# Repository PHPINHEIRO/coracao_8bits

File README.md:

# coracao_8bits
um projeto de uma relogio usando um display de 7 segmentos + arduino pro mini e RTC em formato de um coracao em graficos de 8bits

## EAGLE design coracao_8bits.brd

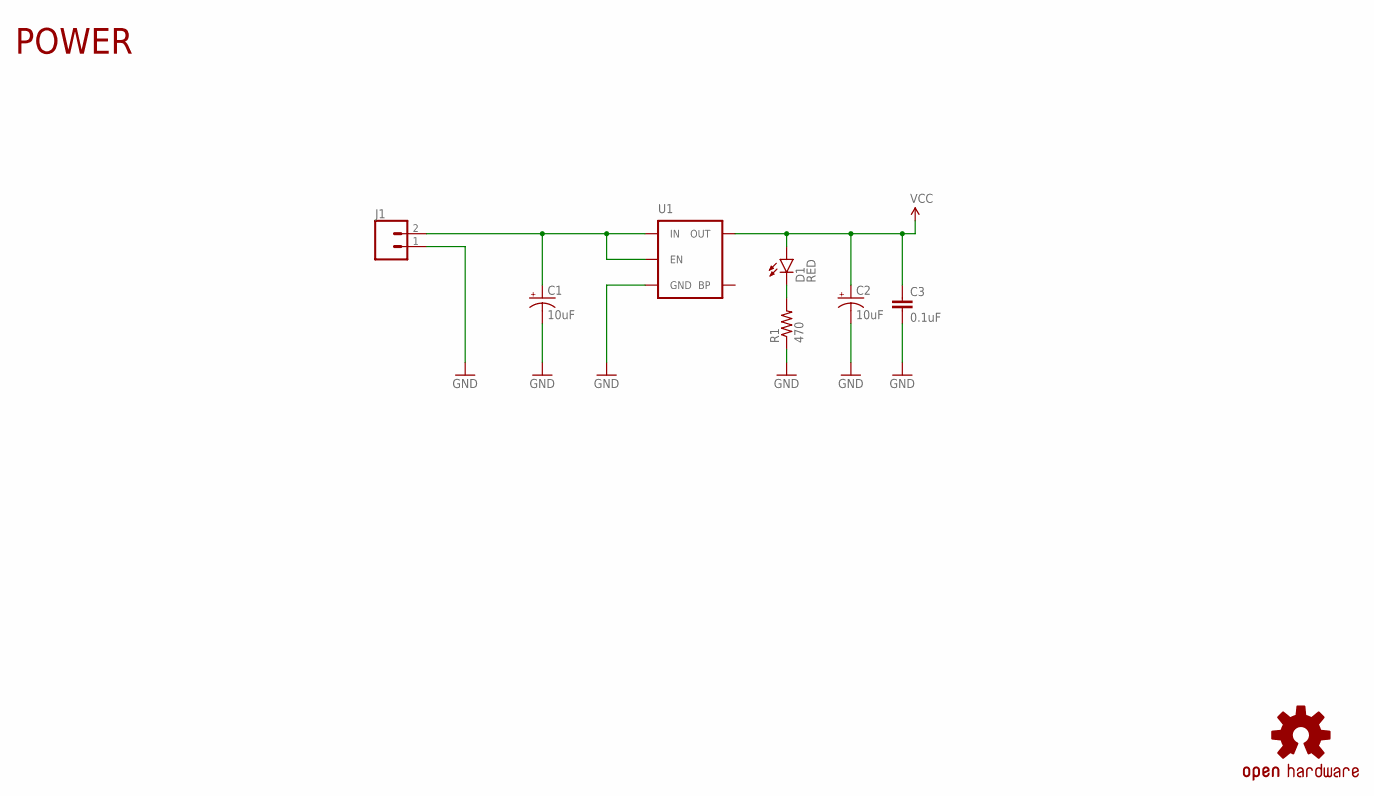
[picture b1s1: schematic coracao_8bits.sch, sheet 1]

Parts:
C1, C2: 10uF; EIA3216
C3: 0.1uF; 0603-CAP
D1: RED; LED-0603
J1: CONN_02; 1X02
LOGO1: OSHW-LOGOMINI; OSHW-LOGO-MINI
R1: 470; 0603-RES
U1: MIC52053.3V; SOT23-5

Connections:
DEETE: C1.A (+), J1.2, U1.1 (IN), U1.3 (EN)
GND: C1.C (-), C2.C (-), C3.2, J1.1, R1.1, U1.2 (GND); also elsewhere on the board
unnamed: D1.C, R1.2
VCC: C2.A (+), C3.1, D1.A, U1.5 (OUT); also elsewhere on the board

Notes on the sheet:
POWER

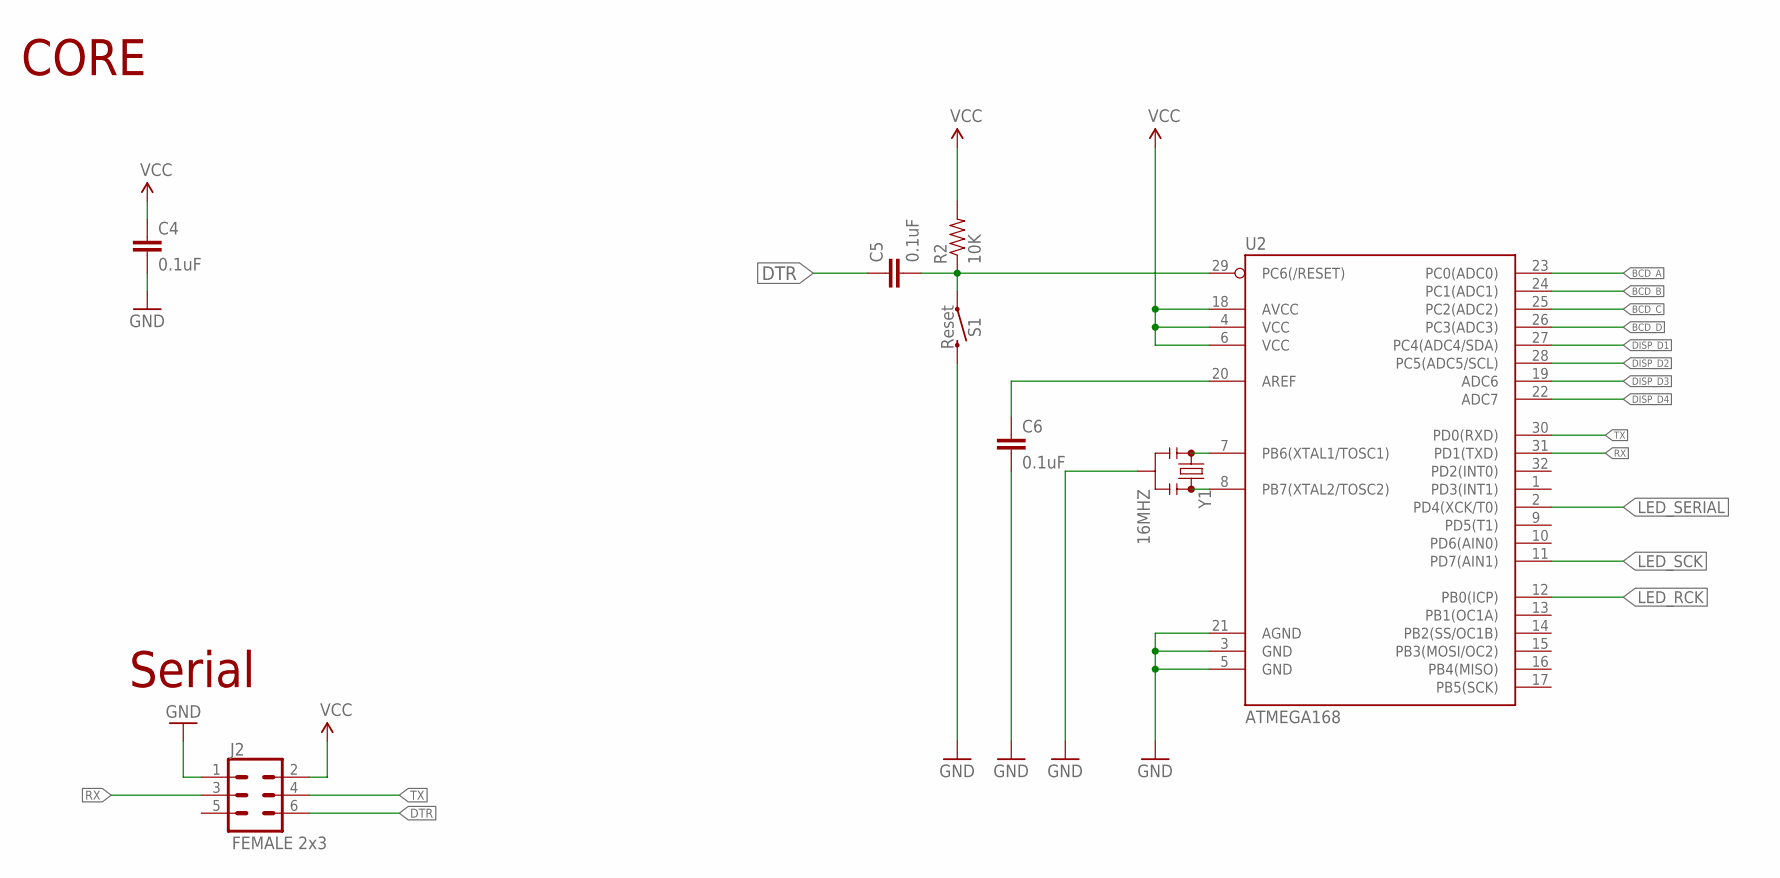
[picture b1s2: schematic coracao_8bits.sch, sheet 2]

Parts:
C4, C5, C6: 0.1uF; 0603-CAP
J2: FEMALE 2x3; 2X3
R2: 10K; 0603-RES
S1: Reset; TACTILE_SWITCH_SMD_6.0X3.5MM
U2: ATMEGA168; TQFP32-08
Y1: 16MHZ; RESONATOR-SMD

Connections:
BCD_A: U2.23 (PC0(ADC0)); also elsewhere on the board
BCD_B: U2.24 (PC1(ADC1)); also elsewhere on the board
BCD_C: U2.25 (PC2(ADC2)); also elsewhere on the board
BCD_D: U2.26 (PC3(ADC3)); also elsewhere on the board
DISP_D1: U2.27 (PC4(ADC4/SDA)); also elsewhere on the board
DISP_D2: U2.28 (PC5(ADC5/SCL)); also elsewhere on the board
DISP_D3: U2.19 (ADC6); also elsewhere on the board
DISP_D4: U2.22 (ADC7); also elsewhere on the board
DTR: C5.1, J2.6
GND: C4.2, C6.2, J2.1, S1.2, U2.3 (GND), U2.5 (GND), U2.21 (AGND), Y1.2; also elsewhere on the board
LED_RCK: U2.12 (PB0(ICP)); also elsewhere on the board
LED_SCK: U2.11 (PD7(AIN1)); also elsewhere on the board
LED_SERIAL: U2.2 (PD4(XCK/T0)); also elsewhere on the board
unnamed: U2.7 (PB6(XTAL1/TOSC1)), Y1.1
unnamed: U2.8 (PB7(XTAL2/TOSC2)), Y1.3
unnamed: C6.1, U2.20 (AREF)
unnamed: C5.2, R2.1, S1.1, U2.29 (PC6(/RESET))
RX: J2.3, U2.31 (PD1(TXD))
TX: J2.4, U2.30 (PD0(RXD))
VCC: C4.1, J2.2, R2.2, U2.4 (VCC), U2.6 (VCC), U2.18 (AVCC); also elsewhere on the board

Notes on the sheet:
CORE
Serial

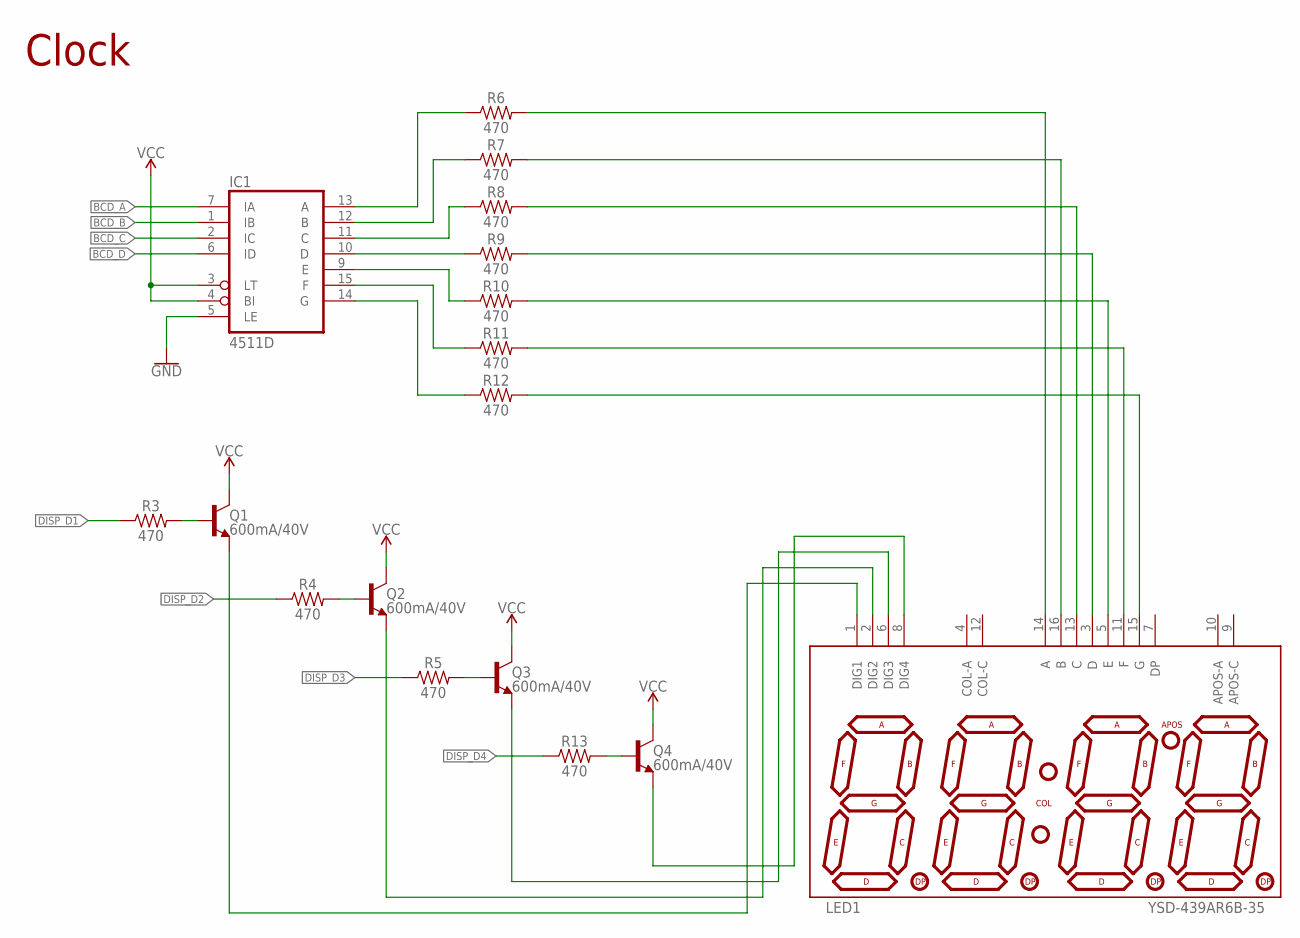
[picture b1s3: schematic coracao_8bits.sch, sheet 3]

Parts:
IC1: 4511D; SO16
LED1: YSD-439AR6B-35; 7-SEGMENT-4DIGIT-YOUNGSUN
Q1, Q2, Q3, Q4: 600mA/40V; SOT23-3
R3, R4, R5, R6, R7, R8, R9, R10, R11, R12, R13: 470; 0603

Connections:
BCD_A: IC1.7 (IA); also elsewhere on the board
BCD_B: IC1.1 (IB); also elsewhere on the board
BCD_C: IC1.2 (IC); also elsewhere on the board
BCD_D: IC1.6 (ID); also elsewhere on the board
DISP_D1: R3.1; also elsewhere on the board
DISP_D2: R4.1; also elsewhere on the board
DISP_D3: R5.1; also elsewhere on the board
DISP_D4: R13.1; also elsewhere on the board
GND: IC1.5 (LE); also elsewhere on the board
unnamed: IC1.10 (D), R9.1
unnamed: IC1.11 (C), R8.1
unnamed: IC1.12 (B), R7.1
unnamed: IC1.13 (A), R6.1
unnamed: IC1.9 (E), R10.1
unnamed: IC1.15 (F), R11.1
unnamed: IC1.14 (G), R12.1
unnamed: LED1.14 (A), R6.2
unnamed: LED1.16 (B), R7.2
unnamed: LED1.13 (C), R8.2
unnamed: LED1.3 (D), R9.2
unnamed: LED1.5 (E), R10.2
unnamed: LED1.11 (F), R11.2
unnamed: LED1.15 (G), R12.2
unnamed: LED1.8 (DIG4), Q4.2 (E)
unnamed: LED1.6 (DIG3), Q3.2 (E)
unnamed: LED1.2 (DIG2), Q2.2 (E)
unnamed: LED1.1 (DIG1), Q1.2 (E)
unnamed: Q2.1 (B), R4.2
unnamed: Q4.1 (B), R13.2
unnamed: Q3.1 (B), R5.2
unnamed: Q1.1 (B), R3.2
VCC: IC1.3 (LT), IC1.4 (BI), Q1.3 (C), Q2.3 (C), Q3.3 (C), Q4.3 (C); also elsewhere on the board
VDD: IC1.16 (VDD)
VSS: IC1.8 (VSS)

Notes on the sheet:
Clock

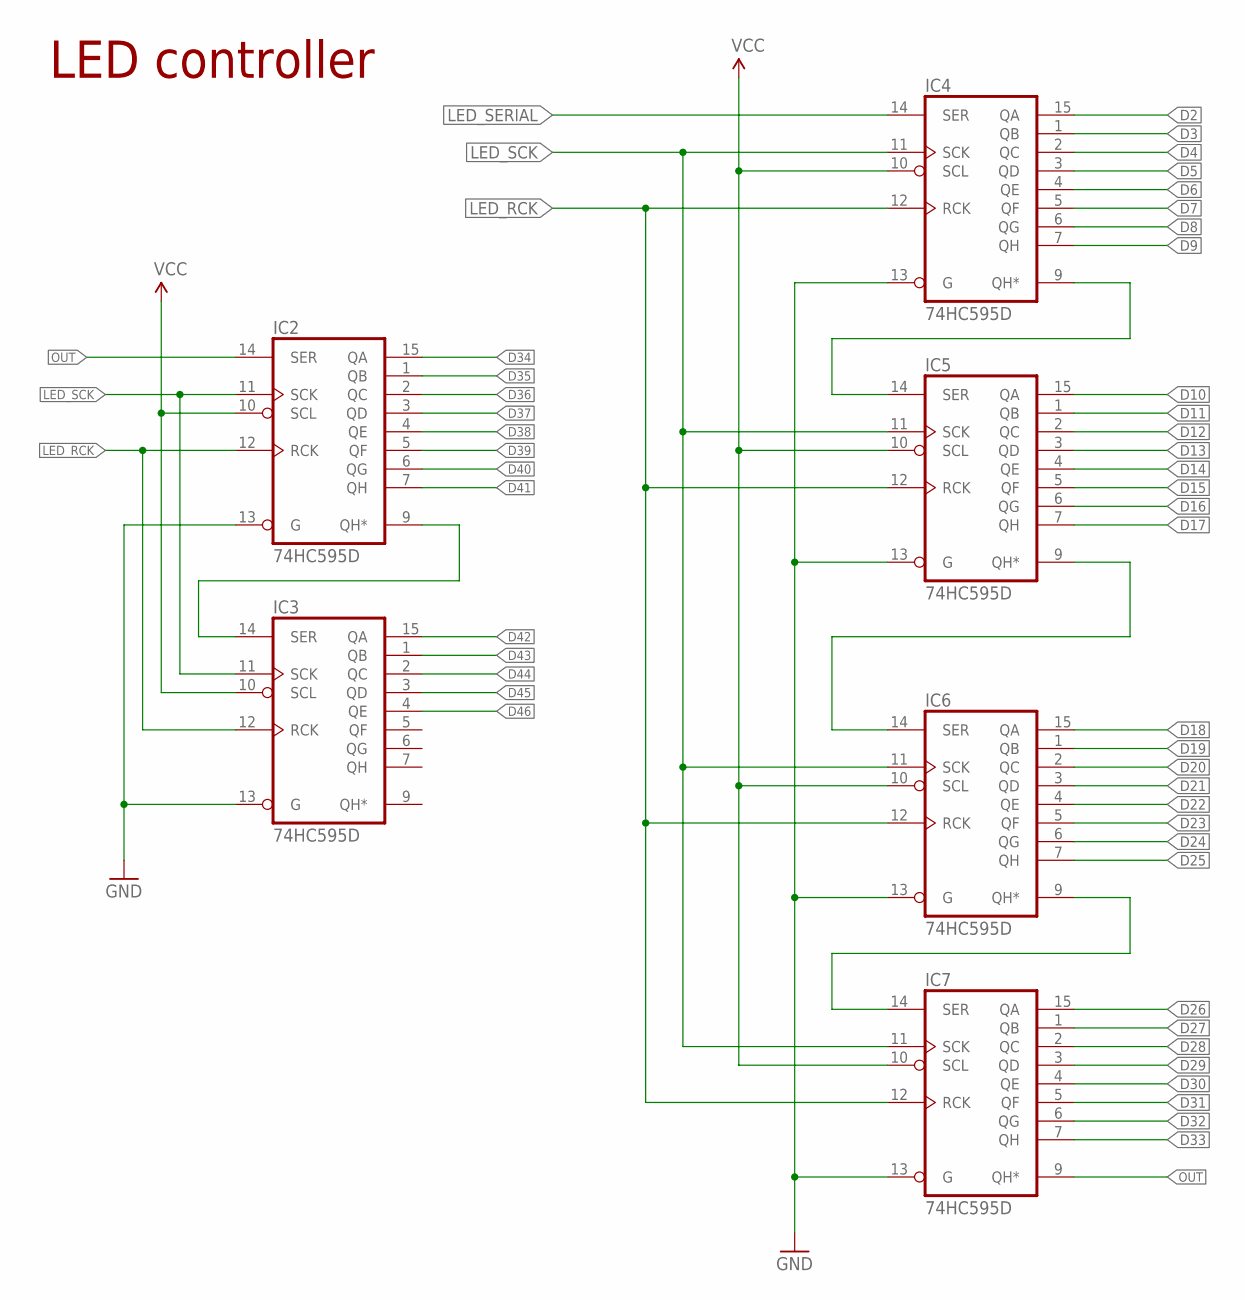
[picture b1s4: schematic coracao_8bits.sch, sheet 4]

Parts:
IC2, IC3, IC4, IC5, IC6, IC7: 74HC595D; SO16

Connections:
D2: IC4.15 (QA); also elsewhere on the board
D3: IC4.1 (QB); also elsewhere on the board
D4: IC4.2 (QC); also elsewhere on the board
D5: IC4.3 (QD); also elsewhere on the board
D6: IC4.4 (QE); also elsewhere on the board
D7: IC4.5 (QF); also elsewhere on the board
D8: IC4.6 (QG); also elsewhere on the board
D9: IC4.7 (QH); also elsewhere on the board
D10: IC5.15 (QA); also elsewhere on the board
D11: IC5.1 (QB); also elsewhere on the board
D12: IC5.2 (QC); also elsewhere on the board
D13: IC5.3 (QD); also elsewhere on the board
D14: IC5.4 (QE); also elsewhere on the board
D15: IC5.5 (QF); also elsewhere on the board
D16: IC5.6 (QG); also elsewhere on the board
D17: IC5.7 (QH); also elsewhere on the board
D18: IC6.15 (QA); also elsewhere on the board
D19: IC6.1 (QB); also elsewhere on the board
D20: IC6.2 (QC); also elsewhere on the board
D21: IC6.3 (QD); also elsewhere on the board
D22: IC6.4 (QE); also elsewhere on the board
D23: IC6.5 (QF); also elsewhere on the board
D24: IC6.6 (QG); also elsewhere on the board
D25: IC6.7 (QH); also elsewhere on the board
D26: IC7.15 (QA); also elsewhere on the board
D27: IC7.1 (QB); also elsewhere on the board
D28: IC7.2 (QC); also elsewhere on the board
D29: IC7.3 (QD); also elsewhere on the board
D30: IC7.4 (QE); also elsewhere on the board
D31: IC7.5 (QF); also elsewhere on the board
D32: IC7.6 (QG); also elsewhere on the board
D33: IC7.7 (QH); also elsewhere on the board
D34: IC2.15 (QA); also elsewhere on the board
D35: IC2.1 (QB); also elsewhere on the board
D36: IC2.2 (QC); also elsewhere on the board
D37: IC2.3 (QD); also elsewhere on the board
D38: IC2.4 (QE); also elsewhere on the board
D39: IC2.5 (QF); also elsewhere on the board
D40: IC2.6 (QG); also elsewhere on the board
D41: IC2.7 (QH); also elsewhere on the board
D42: IC3.15 (QA); also elsewhere on the board
D43: IC3.1 (QB); also elsewhere on the board
D44: IC3.2 (QC); also elsewhere on the board
D45: IC3.3 (QD); also elsewhere on the board
D46: IC3.4 (QE); also elsewhere on the board
GND: IC2.8 (GND), IC2.13 (G), IC3.8 (GND), IC3.13 (G), IC4.8 (GND), IC4.13 (G), IC5.8 (GND), IC5.13 (G), IC6.8 (GND), IC6.13 (G), IC7.8 (GND), IC7.13 (G); also elsewhere on the board
LED_RCK: IC2.12 (RCK), IC3.12 (RCK), IC4.12 (RCK), IC5.12 (RCK), IC6.12 (RCK), IC7.12 (RCK); also elsewhere on the board
LED_SCK: IC2.11 (SCK), IC3.11 (SCK), IC4.11 (SCK), IC5.11 (SCK), IC6.11 (SCK), IC7.11 (SCK); also elsewhere on the board
LED_SERIAL: IC4.14 (SER); also elsewhere on the board
unnamed: IC4.9 (QH*), IC5.14 (SER)
unnamed: IC6.9 (QH*), IC7.14 (SER)
unnamed: IC2.9 (QH*), IC3.14 (SER)
unnamed: IC5.9 (QH*), IC6.14 (SER)
OUT: IC2.14 (SER), IC7.9 (QH*)
VCC: IC2.10 (SCL), IC2.16 (VCC), IC3.10 (SCL), IC3.16 (VCC), IC4.10 (SCL), IC4.16 (VCC), IC5.10 (SCL), IC5.16 (VCC), IC6.10 (SCL), IC6.16 (VCC), IC7.10 (SCL), IC7.16 (VCC); also elsewhere on the board

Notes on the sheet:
LED controller

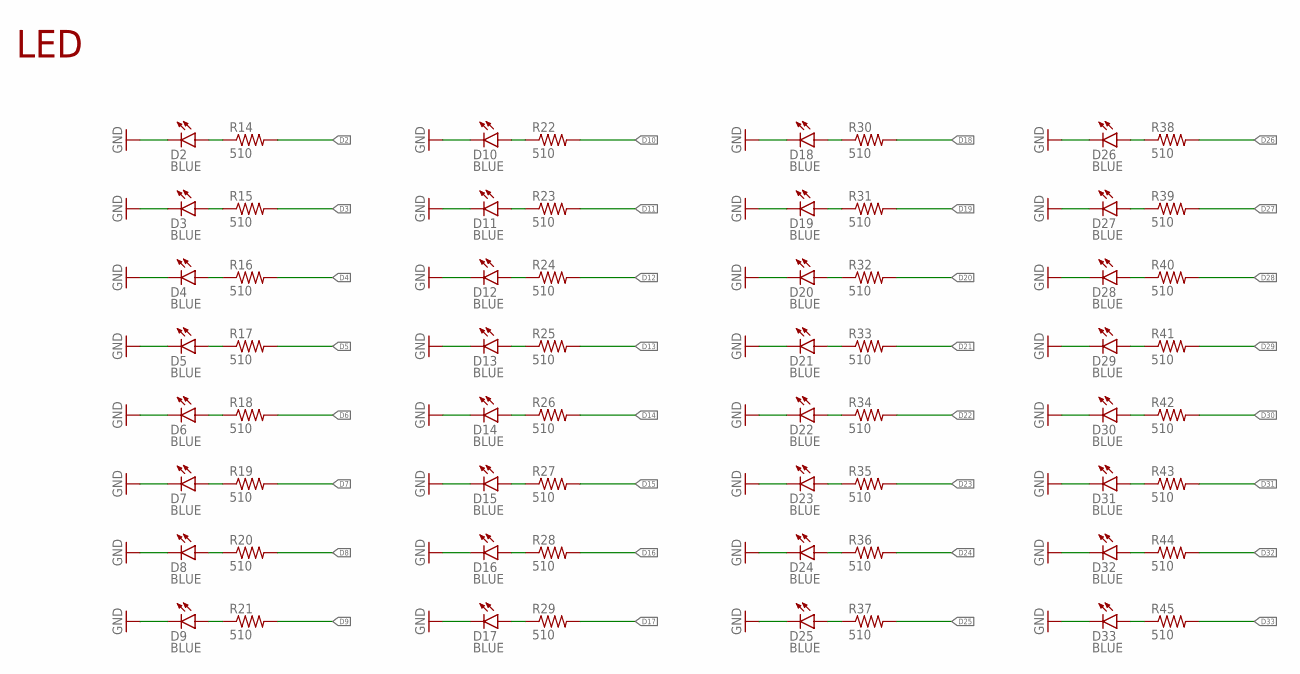
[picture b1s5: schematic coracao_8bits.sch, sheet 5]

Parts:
D2, D3, D4, D5, D6, D7, D8, D9, D10, D11, D12, D13, D14, D15, D16, D17, D18, D19, D20, D21, D22, D23, D24, D25, D26, D27, D28, D29, D30, D31, D32, D33: BLUE; LED-0603
R14, R15, R16, R17, R18, R19, R20, R21, R22, R23, R24, R25, R26, R27, R28, R29, R30, R31, R32, R33, R34, R35, R36, R37, R38, R39, R40, R41, R42, R43, R44, R45: 510; 0603-RES

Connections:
D2: R14.2; also elsewhere on the board
D3: R15.2; also elsewhere on the board
D4: R16.2; also elsewhere on the board
D5: R17.2; also elsewhere on the board
D6: R18.2; also elsewhere on the board
D7: R19.2; also elsewhere on the board
D8: R20.2; also elsewhere on the board
D9: R21.2; also elsewhere on the board
D10: R22.2; also elsewhere on the board
D11: R23.2; also elsewhere on the board
D12: R24.2; also elsewhere on the board
D13: R25.2; also elsewhere on the board
D14: R26.2; also elsewhere on the board
D15: R27.2; also elsewhere on the board
D16: R28.2; also elsewhere on the board
D17: R29.2; also elsewhere on the board
D18: R30.2; also elsewhere on the board
D19: R31.2; also elsewhere on the board
D20: R32.2; also elsewhere on the board
D21: R33.2; also elsewhere on the board
D22: R34.2; also elsewhere on the board
D23: R35.2; also elsewhere on the board
D24: R36.2; also elsewhere on the board
D25: R37.2; also elsewhere on the board
D26: R38.2; also elsewhere on the board
D27: R39.2; also elsewhere on the board
D28: R40.2; also elsewhere on the board
D29: R41.2; also elsewhere on the board
D30: R42.2; also elsewhere on the board
D31: R43.2; also elsewhere on the board
D32: R44.2; also elsewhere on the board
D33: R45.2; also elsewhere on the board
GND: D2.C, D3.C, D4.C, D5.C, D6.C, D7.C, D8.C, D9.C, D10.C, D11.C, D12.C, D13.C, D14.C, D15.C, D16.C, D17.C, D18.C, D19.C, D20.C, D21.C, D22.C, D23.C, D24.C, D25.C, D26.C, D27.C, D28.C, D29.C, D30.C, D31.C, D32.C, D33.C; also elsewhere on the board
unnamed: D2.A, R14.1
unnamed: D3.A, R15.1
unnamed: D4.A, R16.1
unnamed: D5.A, R17.1
unnamed: D6.A, R18.1
unnamed: D7.A, R19.1
unnamed: D8.A, R20.1
unnamed: D9.A, R21.1
unnamed: D10.A, R22.1
unnamed: D11.A, R23.1
unnamed: D12.A, R24.1
unnamed: D13.A, R25.1
unnamed: D14.A, R26.1
unnamed: D15.A, R27.1
unnamed: D16.A, R28.1
unnamed: D17.A, R29.1
unnamed: D18.A, R30.1
unnamed: D19.A, R31.1
unnamed: D20.A, R32.1
unnamed: D21.A, R33.1
unnamed: D22.A, R34.1
unnamed: D23.A, R35.1
unnamed: D24.A, R36.1
unnamed: D25.A, R37.1
unnamed: D26.A, R38.1
unnamed: D27.A, R39.1
unnamed: D28.A, R40.1
unnamed: D29.A, R41.1
unnamed: D30.A, R42.1
unnamed: D31.A, R43.1
unnamed: D32.A, R44.1
unnamed: D33.A, R45.1

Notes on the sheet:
LED

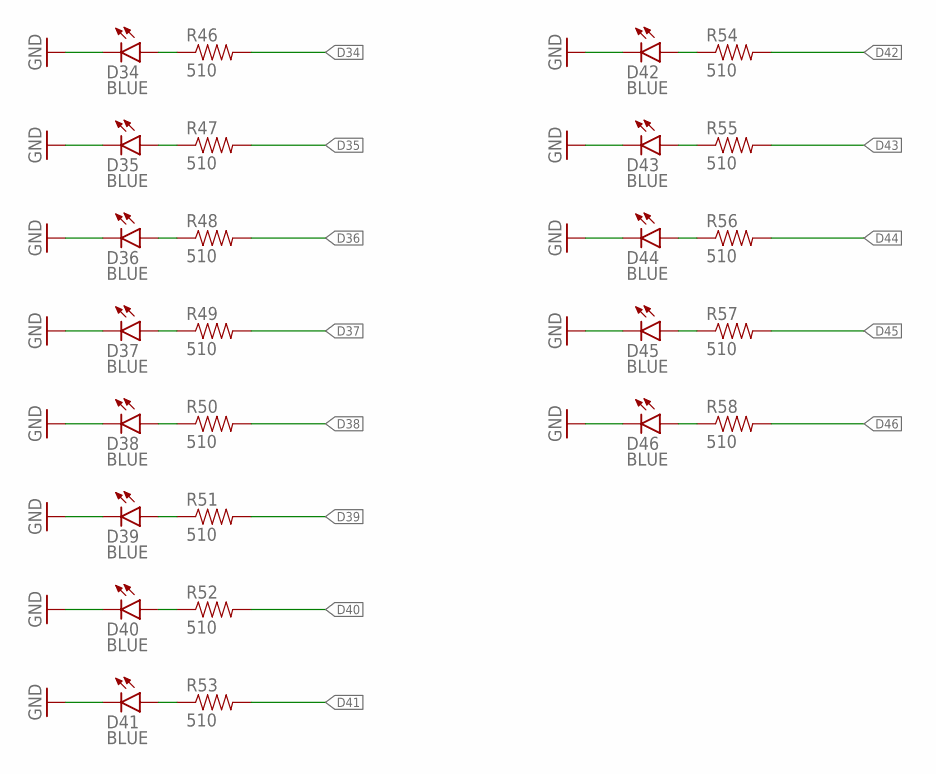
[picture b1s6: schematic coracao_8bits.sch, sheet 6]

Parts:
D34, D35, D36, D37, D38, D39, D40, D41, D42, D43, D44, D45, D46: BLUE; LED-0603
R46, R47, R48, R49, R50, R51, R52, R53, R54, R55, R56, R57, R58: 510; 0603-RES

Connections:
D34: R46.2; also elsewhere on the board
D35: R47.2; also elsewhere on the board
D36: R48.2; also elsewhere on the board
D37: R49.2; also elsewhere on the board
D38: R50.2; also elsewhere on the board
D39: R51.2; also elsewhere on the board
D40: R52.2; also elsewhere on the board
D41: R53.2; also elsewhere on the board
D42: R54.2; also elsewhere on the board
D43: R55.2; also elsewhere on the board
D44: R56.2; also elsewhere on the board
D45: R57.2; also elsewhere on the board
D46: R58.2; also elsewhere on the board
GND: D34.C, D35.C, D36.C, D37.C, D38.C, D39.C, D40.C, D41.C, D42.C, D43.C, D44.C, D45.C, D46.C; also elsewhere on the board
unnamed: D34.A, R46.1
unnamed: D35.A, R47.1
unnamed: D36.A, R48.1
unnamed: D37.A, R49.1
unnamed: D38.A, R50.1
unnamed: D39.A, R51.1
unnamed: D40.A, R52.1
unnamed: D41.A, R53.1
unnamed: D42.A, R54.1
unnamed: D43.A, R55.1
unnamed: D44.A, R56.1
unnamed: D45.A, R57.1
unnamed: D46.A, R58.1

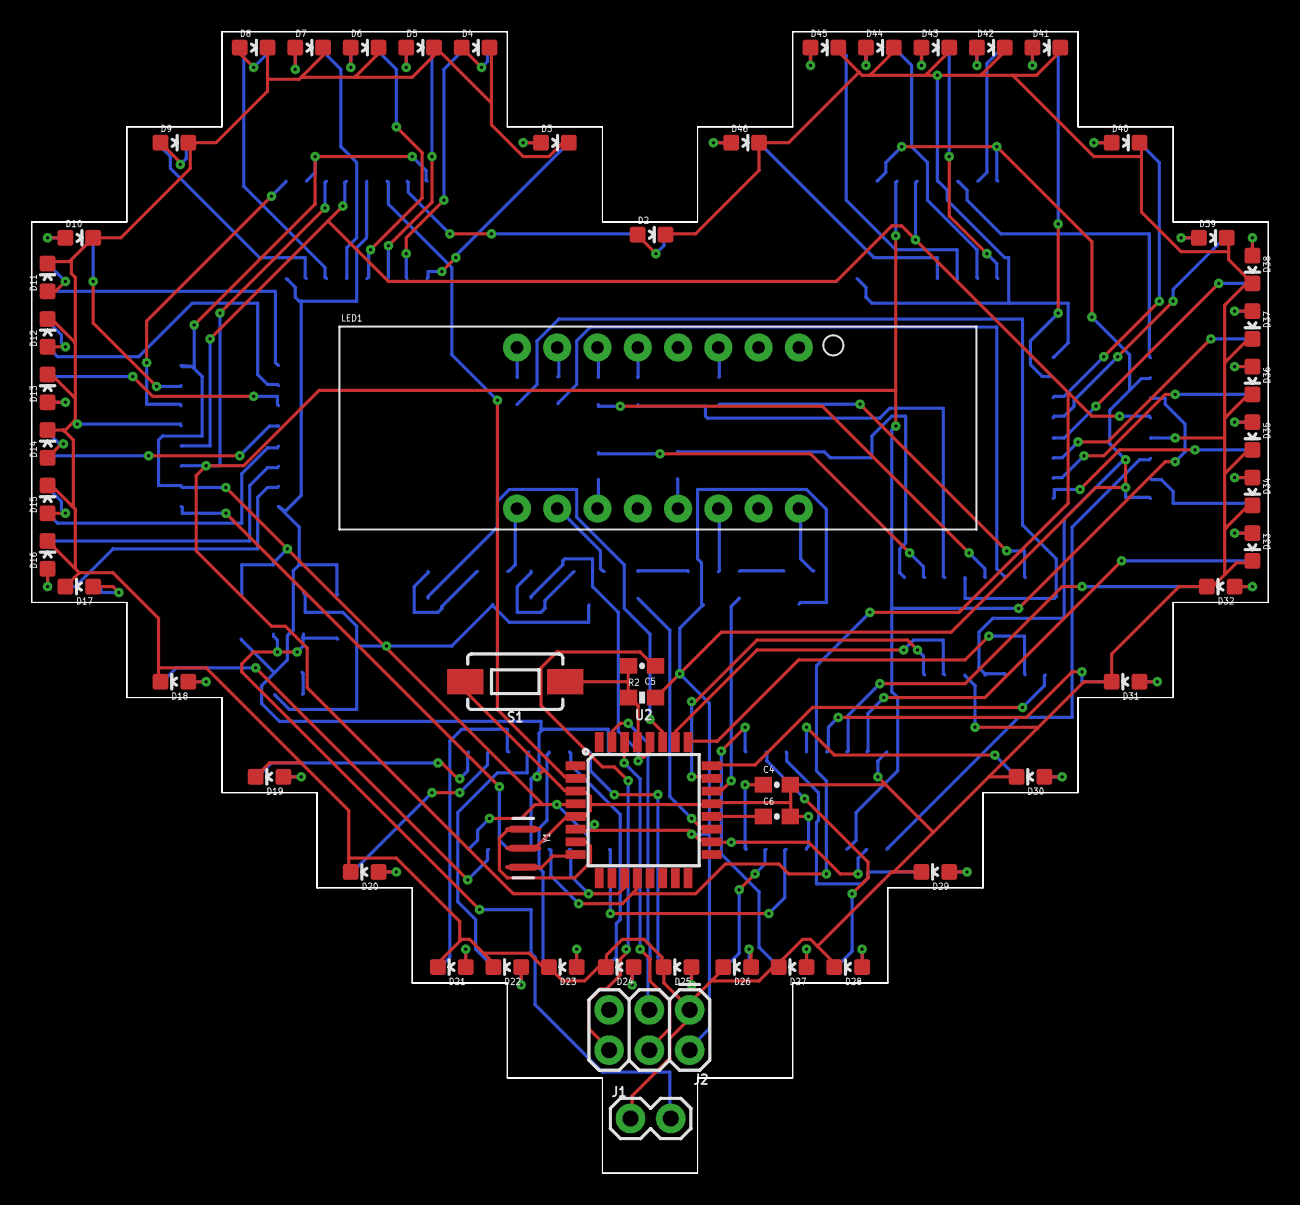
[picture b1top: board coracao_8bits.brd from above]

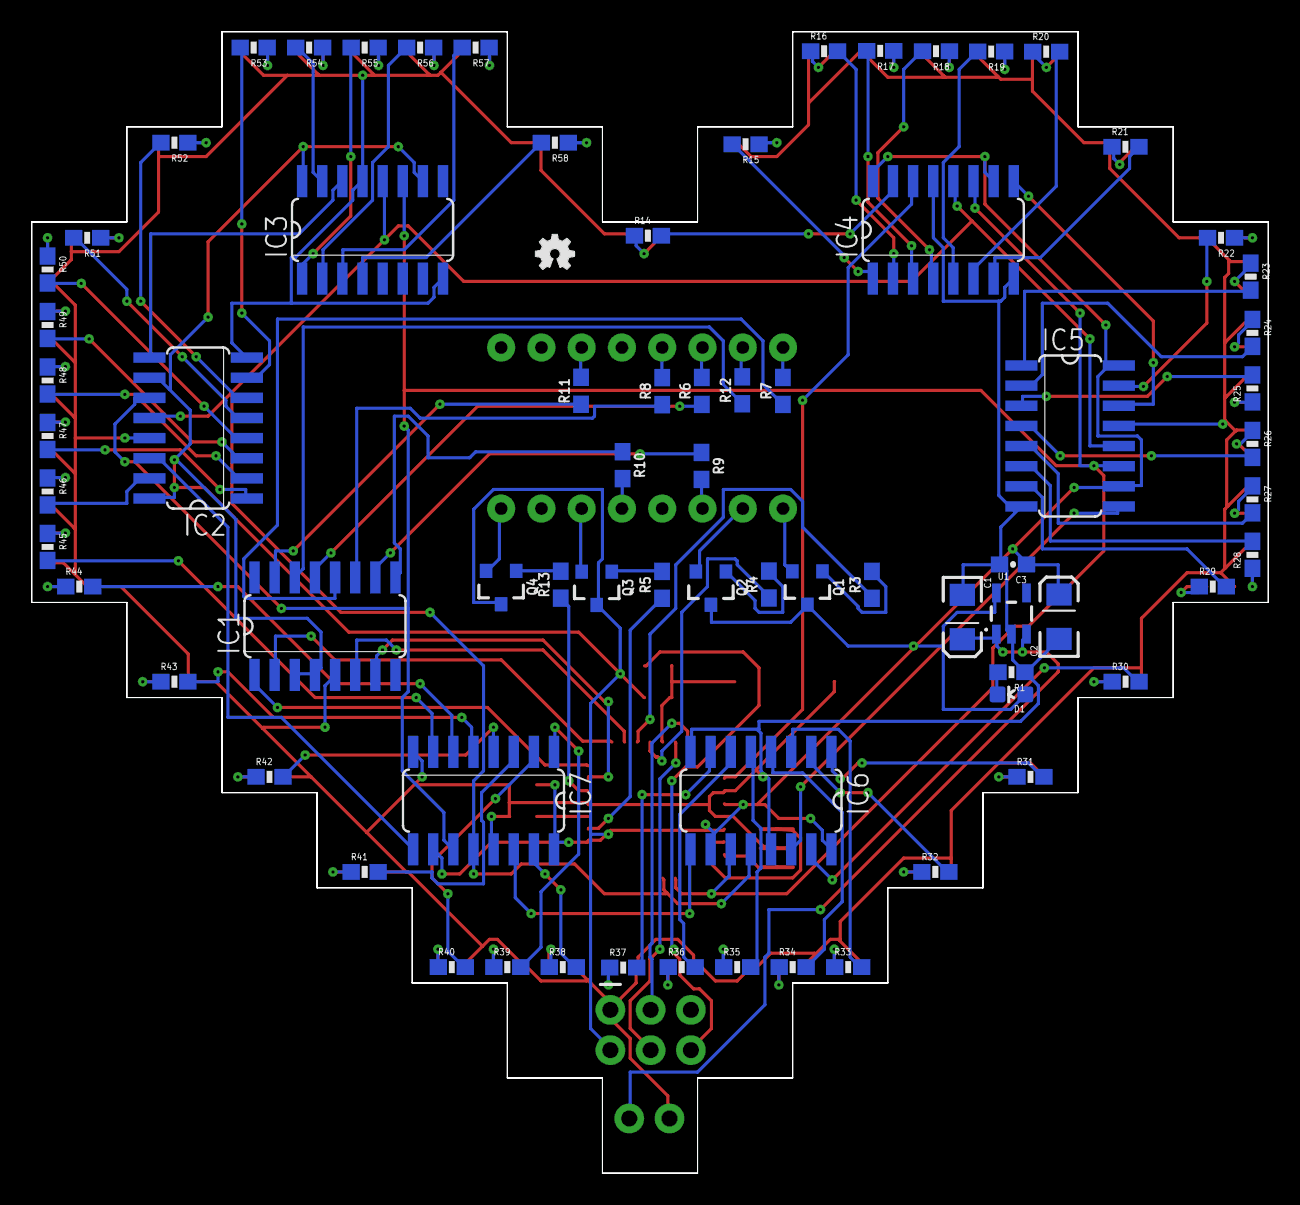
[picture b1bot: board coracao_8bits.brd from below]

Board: 2 copper layers, 78.0 x 72.0 mm, 129 parts (74 on the bottom side), 139 nets.

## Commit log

2017-05-13 primeiro commite
2017-05-15 add power jack
2017-05-17 adicionado mais 2 CIs e mais LEDs, total 45
2017-05-17 finalizada
2017-05-17 adicionado layer milling e finalizando
2017-05-17 upando gerber

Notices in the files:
parts and their libraries:
SparkFun-LED: Licensing: Creative Commons ShareAlike 4.0 International - https://creativecommons.org/licenses/by-sa/4.0
